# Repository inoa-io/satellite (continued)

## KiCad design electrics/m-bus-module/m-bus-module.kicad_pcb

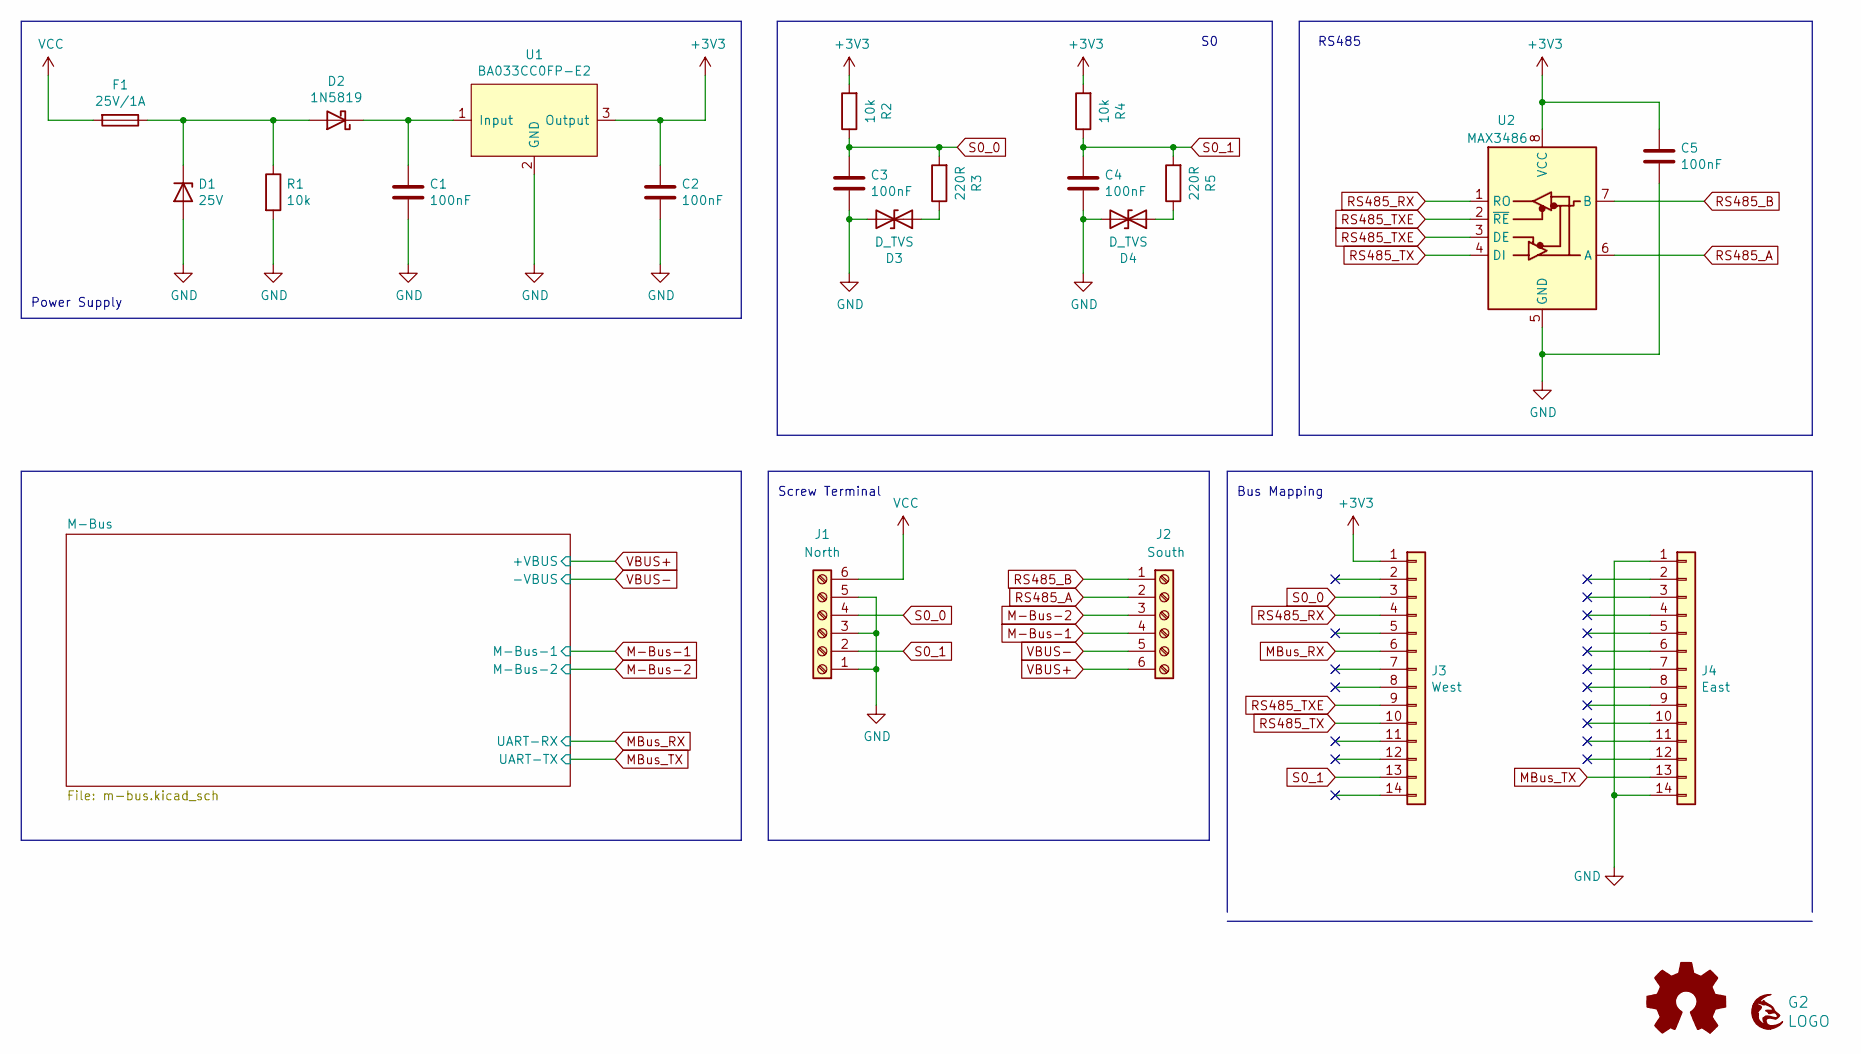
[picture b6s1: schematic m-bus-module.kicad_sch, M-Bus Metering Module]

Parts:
C1, C2, C3, C4: 100nF; C_1206_3216Metric_Pad1.33x1.80mm_HandSolder; mouser# 80-C1206C104M6R
C5: 100nF; C_0603_1608Metric_Pad1.08x0.95mm_HandSolder; mouser# 80-C1206C104M6R
D1: 25V; D_SOD-523; mouser# 750-CPDU24V
D2: 1N5819; D_SOD-323_HandSoldering; mouser# 771-PMEG4010CEAX
D3, D4: D_TVS; D_0603_1608Metric_Pad1.05x0.95mm_HandSolder; mouser# 652-CG0603MLC-3.3LE
F1: 25V/1A; Fuse_1206_3216Metric_Pad1.42x1.75mm_HandSolder; mouser# 504-TR/3216FF1-R
G1: Logo_Open_Hardware_Small; OSHW-Logo2_7.3x6mm_SilkScreen
G2: LOGO; grayc-logo-negative
J1: North; PHOENIX_1935200; mouser# 651-1935200
J2: South; PHOENIX_1935200; mouser# 651-1935200
J3: West; PinHeader_1x14_P2.54mm_Vertical; mouser# 855-M20-9991446
J4: East; PinHeader_1x14_P2.54mm_Vertical; mouser# 855-M20-9991446
R1, R2, R4: 10k; R_1206_3216Metric_Pad1.30x1.75mm_HandSolder; mouser# 652-CR1206JW-103ELF
R3, R5: 220R; R_1206_3216Metric_Pad1.30x1.75mm_HandSolder; mouser# 652-CR0603FX-2200ELF
U1: BA033CC0FP-E2; TO-252-3_TabPin2; mouser# 755-BA033CC0FP-E2
U2: MAX3486; SOIC-8_3.9x4.9mm_P1.27mm; mouser# 700-MAX3486EESA

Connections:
+3V3: C2.1, C5.1, J3.1, R2.2, R4.2, U1.3 (Output), U2.8 (VCC); also elsewhere on the board
GND: C1.2, C2.2, C3.2, C4.2, C5.2, D1.2 (A), D3.2 (A2), D4.2 (A2), J1.1, J1.3, J1.5, J4.1, J4.14, R1.2, U1.2 (GND), U2.5 (GND); also elsewhere on the board
GNDS: J2.3, J2.5; also elsewhere on the board
M-Bus: J2.4; also elsewhere on the board
MBus_RX: J3.6; also elsewhere on the board
MBus_TX: J4.13; also elsewhere on the board
unnamed: C1.1, D2.1 (K), U1.1 (Input)
unnamed: D1.1 (K), D2.2 (A), F1.1, R1.1
unnamed: D3.1 (A1), R3.1
unnamed: D4.1 (A1), R5.1
RS485_A: J2.2, U2.6 (A)
RS485_B: J2.1, U2.7 (B)
RS485_RX: J3.4, U2.1 (RO)
RS485_TX: J3.10, U2.4 (DI)
RS485_TXE: J3.9, U2.2 (~RE), U2.3 (DE)
S0_0: C3.1, J1.4, J3.3, R2.1, R3.2
S0_1: C4.1, J1.2, J3.13, R4.1, R5.2
VBUS: J2.6; also elsewhere on the board
VCC: F1.2, J1.6

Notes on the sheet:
Bus Mapping
RS485
Power Supply
Screw Terminal

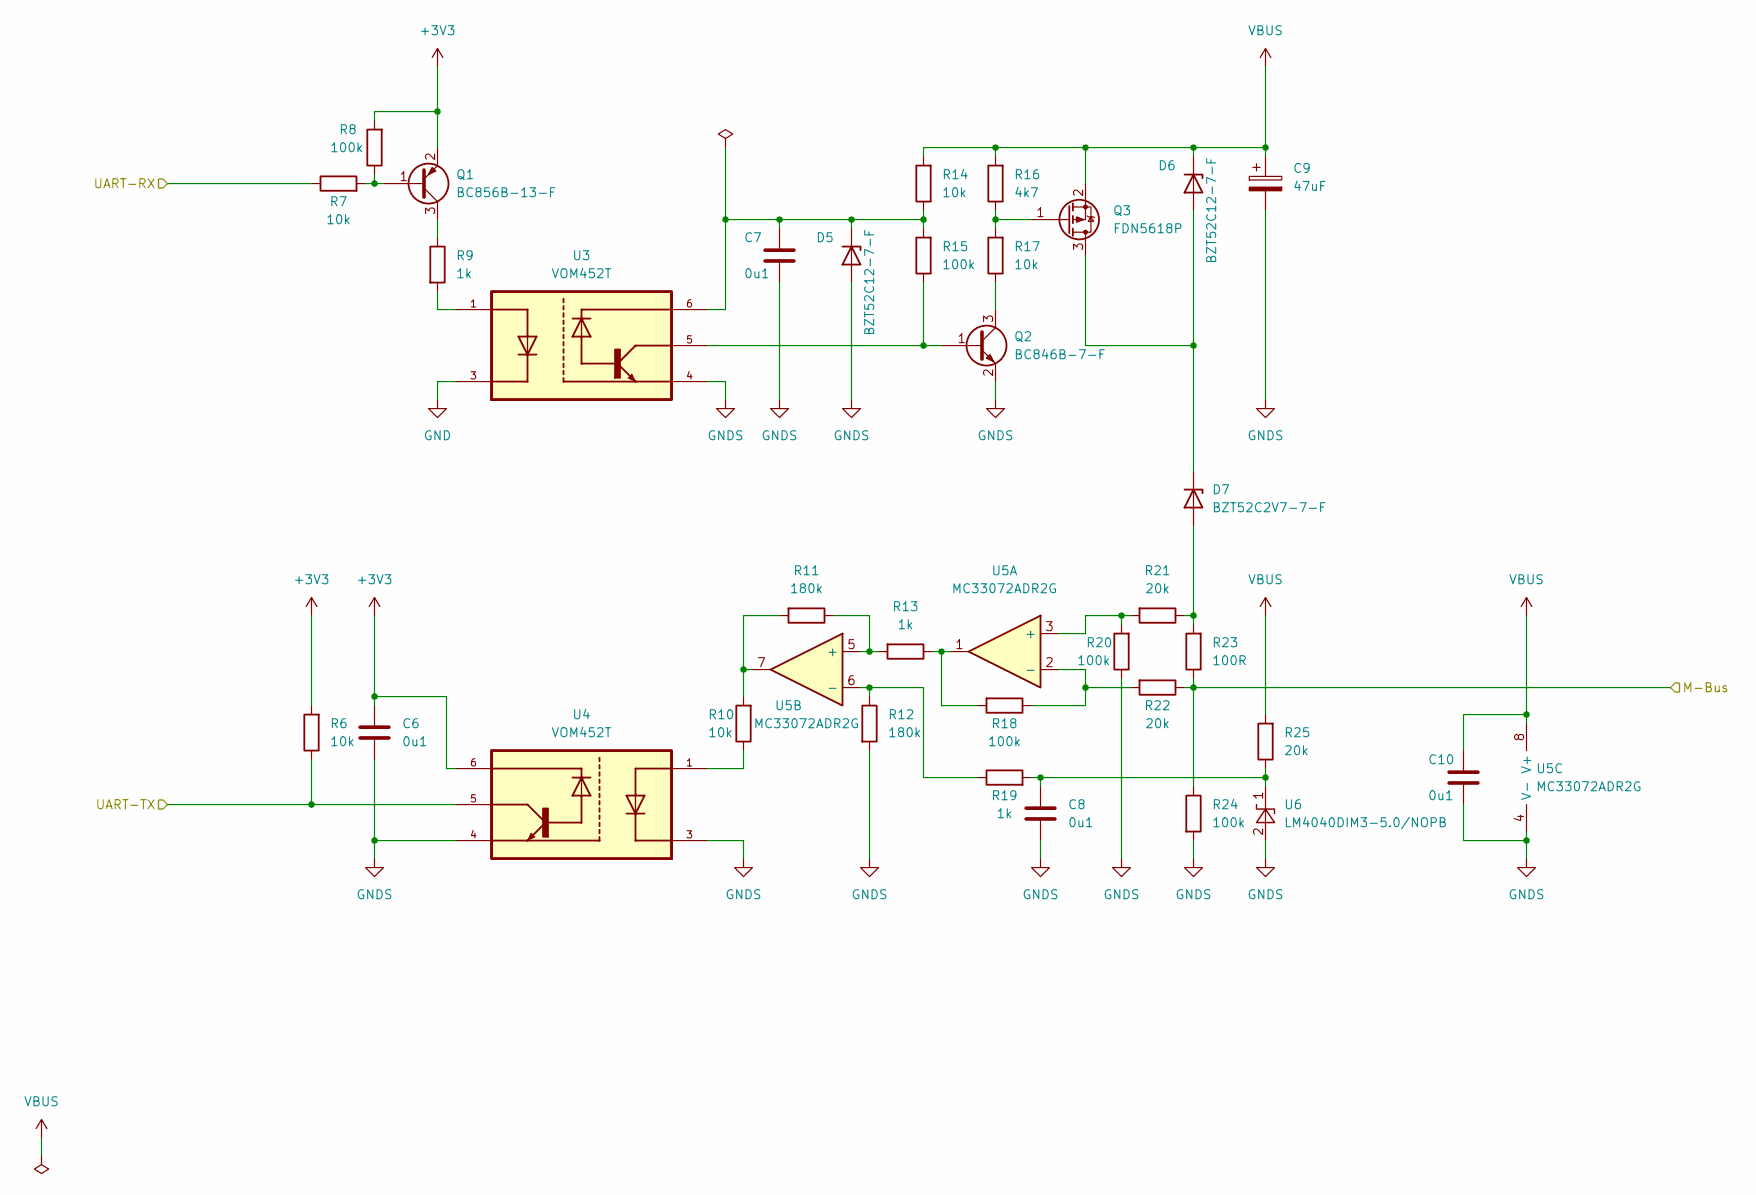
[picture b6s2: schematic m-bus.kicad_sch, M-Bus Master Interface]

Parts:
C6, C7, C8, C10: 0u1; C_0603_1608Metric_Pad1.08x0.95mm_HandSolder; mouser# 80-C0603C104M4R
C9: 47uF; CP_Elec_6.3x7.7; mouser# 80-EDK476M050S9HAA
D5, D6: BZT52C12-7-F; D_SOD-123; mouser# 621-BZT52C12-F
D7: BZT52C2V7-7-F; D_SOD-123; mouser# 621-BZT52C2V7-F
Q1: BC856B-13-F; SOT-23; mouser# 621-BC856B-13-F
Q2: BC846B-7-F; SOT-23; mouser# 621-BC846B-7-F
Q3: FDN5618P; SOT-23; mouser# 78-SI2309CDS-T1-BE3
R6, R7, R10, R14, R17: 10k; R_0603_1608Metric_Pad0.98x0.95mm_HandSolder; mouser# 660-RN73H1TD1002F25
R8, R15, R18, R20, R24: 100k; R_0603_1608Metric_Pad0.98x0.95mm_HandSolder; mouser# 660-RN73H1JTD1003F25
R9, R13, R19: 1k; R_0603_1608Metric_Pad0.98x0.95mm_HandSolder; mouser# 660-RN73H1JTD1001B25
R11, R12: 180k; R_0603_1608Metric_Pad0.98x0.95mm_HandSolder; mouser# 660-RN73H1JTD1803F25
R16: 4k7; R_0603_1608Metric_Pad0.98x0.95mm_HandSolder; mouser# 660-RN73H1JT4701F100
R21, R22, R25: 20k; R_0603_1608Metric_Pad0.98x0.95mm_HandSolder; mouser# 660-RN73H1JTD2002B10
R23: 100R; R_0603_1608Metric_Pad0.98x0.95mm_HandSolder; mouser# 660-RN73H1JTD1000F50
U3, U4: VOM452T; SOIC127P700X230-5N; mouser# 782-VOM452T
U5: MC33072ADR2G; SOIC127P600X175-8N; mouser# 511-LM258ADT
U6: LM4040DIM3-5.0/NOPB; SOT-23; mouser# 926-LM4040DIM350NOPB

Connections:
+3V3: C6.1, Q1.2 (E), R6.2, R8.2, U4.6; also elsewhere on the board
GND: U3.3; also elsewhere on the board
GNDS: C6.2, C7.2, C8.2, C9.2, C10.2, D5.2 (A), Q2.2 (E), R12.2, R20.1, R24.2, U3.4, U4.3, U4.4, U5.4 (V-), U6.2 (A); also elsewhere on the board
M-Bus: R22.1, R23.1, R24.1; also elsewhere on the board
MBus_RX: R7.1; also elsewhere on the board
MBus_TX: R6.1, U4.5; also elsewhere on the board
unnamed: C7.1, D5.1 (K), R14.1, R15.2, U3.6
unnamed: C8.1, R19.2, R25.1, U6.1 (K)
unnamed: D6.2 (A), D7.1 (K), Q3.3 (D)
unnamed: D7.2 (A), R21.1, R23.2
unnamed: Q1.1 (B), R7.2, R8.1
unnamed: Q1.3 (C), R9.1
unnamed: Q2.1 (B), R15.1, U3.5
unnamed: Q2.3 (C), R17.1
unnamed: Q3.1 (G), R16.1, R17.2
unnamed: R9.2, U3.1
unnamed: R10.1, U4.1
unnamed: R10.2, R11.2, U5.7
unnamed: R11.1, R13.2, U5.5 (+)
unnamed: R12.1, R19.1, U5.6 (-)
unnamed: R13.1, R18.2, U5.1
unnamed: R18.1, R22.2, U5.2 (-)
unnamed: R20.2, R21.2, U5.3 (+)
VBUS: C9.1, C10.1, D6.1 (K), Q3.2 (S), R14.2, R16.2, R25.2, U5.8 (V+); also elsewhere on the board

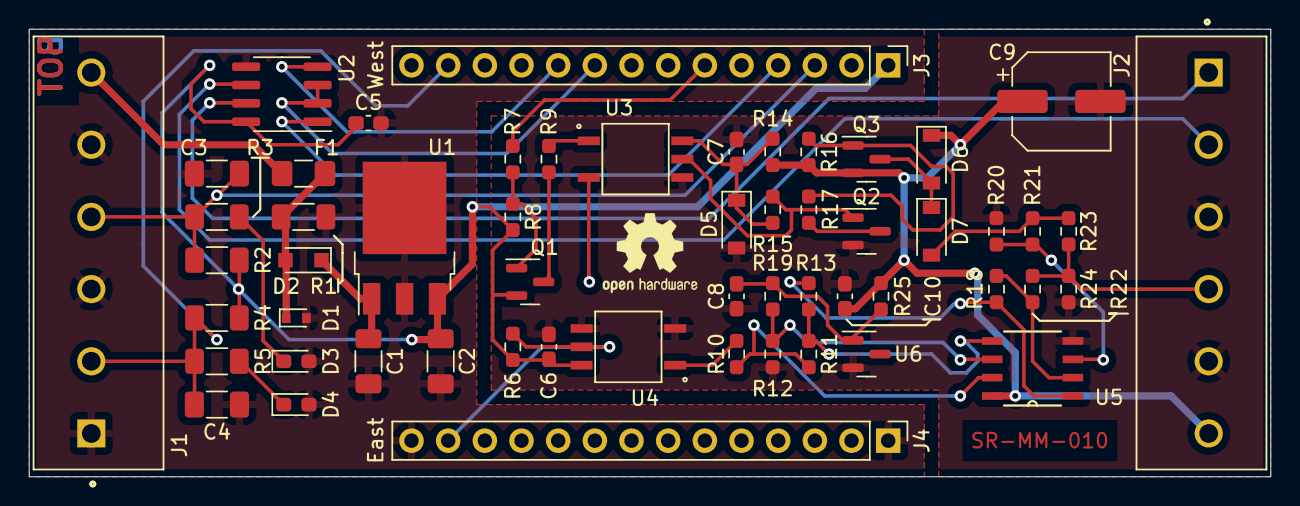
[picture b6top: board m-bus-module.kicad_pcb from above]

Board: 2 copper layers, 86.0 x 31.0 mm, 58 parts (1 on the bottom side), 36 nets.

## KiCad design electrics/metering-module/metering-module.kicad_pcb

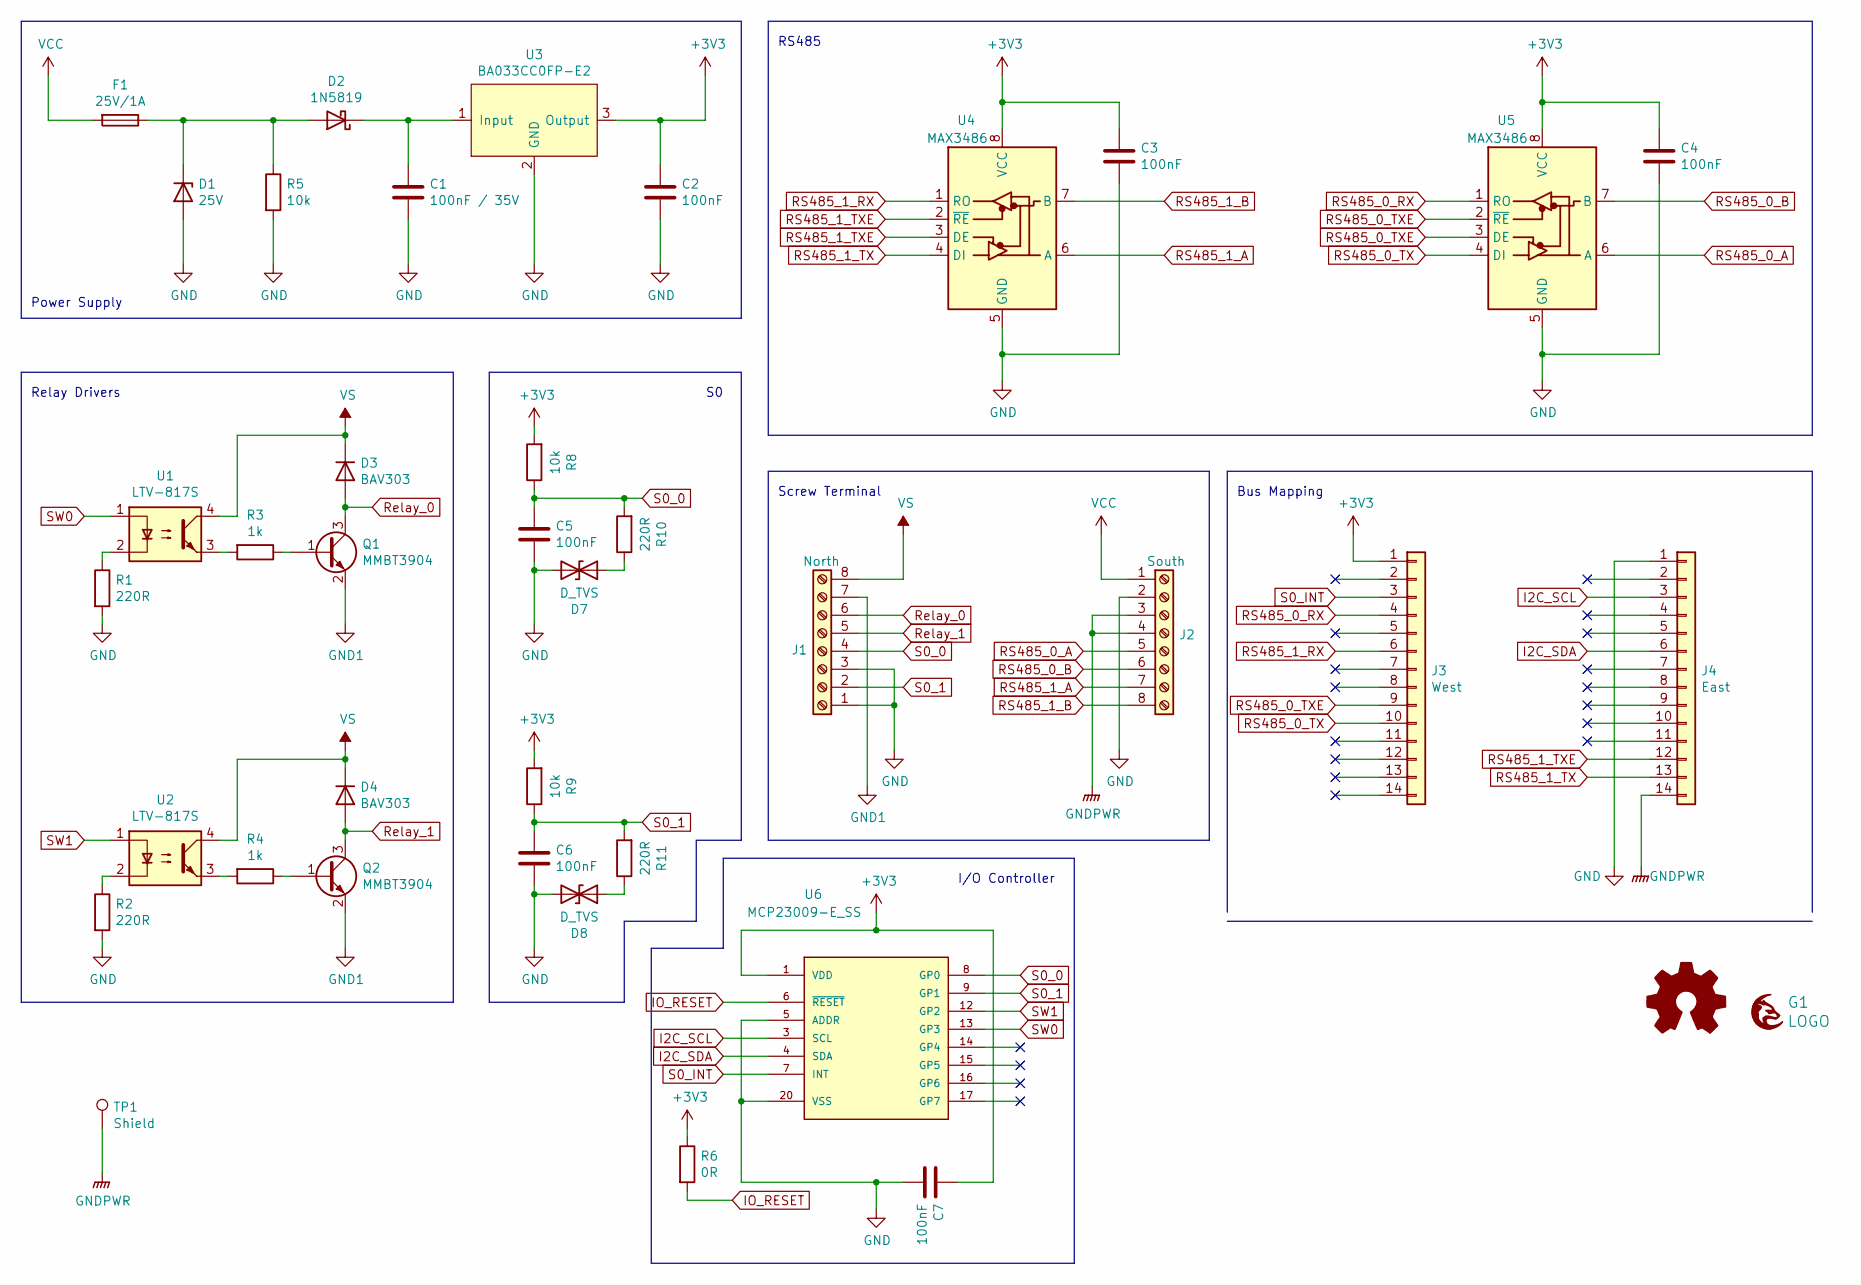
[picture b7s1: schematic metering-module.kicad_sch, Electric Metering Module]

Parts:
C1: 100nF / 35V; C_1206_3216Metric_Pad1.33x1.80mm_HandSolder
C2, C3, C4, C5, C6, C7: 100nF; C_1206_3216Metric_Pad1.33x1.80mm_HandSolder
D1: 25V; D_SOD-523
D2: 1N5819; D_SOD-323_HandSoldering
D3, D4: BAV303; D_MicroMELF
D7, D8: D_TVS; D_0603_1608Metric_Pad1.05x0.95mm_HandSolder
F1: 25V/1A; Fuse_1206_3216Metric_Pad1.42x1.75mm_HandSolder
G1: LOGO; grayc-logo-negative
G2: Logo_Open_Hardware_Small; OSHW-Logo2_7.3x6mm_SilkScreen
J1: North; PHOENIX_1727078
J2: South; PHOENIX_1727078
J3: West; PinHeader_1x14_P2.54mm_Vertical
J4: East; PinHeader_1x14_P2.54mm_Vertical
Q1, Q2: MMBT3904; SOT-23
R1, R2, R10, R11: 220R; R_1206_3216Metric_Pad1.30x1.75mm_HandSolder
R3, R4: 1k; R_1206_3216Metric_Pad1.30x1.75mm_HandSolder
R5, R8, R9: 10k; R_1206_3216Metric_Pad1.30x1.75mm_HandSolder
R6: 0R; R_1206_3216Metric_Pad1.30x1.75mm_HandSolder
TP1: Shield; TestPoint_Pad_D4.0mm
U1, U2: LTV-817S; SMDIP-4_W9.53mm
U3: BA033CC0FP-E2; TO-252-3_TabPin2
U4, U5: MAX3486; SOIC-8_3.9x4.9mm_P1.27mm
U6: MCP23009-E_SS; SOP65P780X200-20N

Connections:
GND: C1.2, C2.2, C3.2, C4.2, C5.2, C6.2, C7.2, D1.2 (A), D7.2 (A2), D8.2 (A2), J1.1, J1.3, J2.2, J4.1, R1.2, R2.2, R5.2, U3.2 (GND), U4.5 (GND), U5.5 (GND), U6.5 (ADDR), U6.20 (VSS)
GND1: J1.7, Q1.2 (E), Q2.2 (E)
GNDPWR: J2.3, J2.4, J4.14, TP1.1
I2C_SCL: J4.3, U6.3 (SCL)
I2C_SDA: J4.6, U6.4 (SDA)
unnamed: C1.1, D2.1 (K), U3.1 (Input)
unnamed: D1.1 (K), D2.2 (A), F1.1, R5.1
unnamed: D7.1 (A1), R10.1
unnamed: D8.1 (A1), R11.1
unnamed: Q1.1 (B), R3.1
unnamed: Q2.1 (B), R4.1
unnamed: R1.1, U1.2
unnamed: R2.1, U2.2
unnamed: R3.2, U1.3
unnamed: R4.2, U2.3
RS485_0_A: J2.5, U5.6 (A)
RS485_0_B: J2.6, U5.7 (B)
RS485_0_RX: J3.4, U5.1 (RO)
RS485_0_TX: J3.10, U5.4 (DI)
RS485_0_TXE: J3.9, U5.2 (~RE), U5.3 (DE)
RS485_1_A: J2.7, U4.6 (A)
RS485_1_B: J2.8, U4.7 (B)
RS485_1_RX: J3.6, U4.1 (RO)
RS485_1_TX: J4.13, U4.4 (DI)
RS485_1_TXE: J4.12, U4.2 (~RE), U4.3 (DE)
Relay_0: D3.2 (A), J1.6, Q1.3 (C)
Relay_1: D4.2 (A), J1.5, Q2.3 (C)
S0_0: C5.1, J1.4, R8.1, R10.2, U6.8 (GP0)
S0_1: C6.1, J1.2, R9.1, R11.2, U6.9 (GP1)
S0_INT: J3.3, U6.7 (INT)
SW0: U1.1, U6.13 (GP3)
SW1: U2.1, U6.12 (GP2)
VCC: F1.2, J2.1
VS: D3.1 (K), D4.1 (K), J1.8, U1.4, U2.4

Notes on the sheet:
Relay Drivers
RS485
Screw Terminal
I/O Controller
Bus Mapping
Power Supply

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
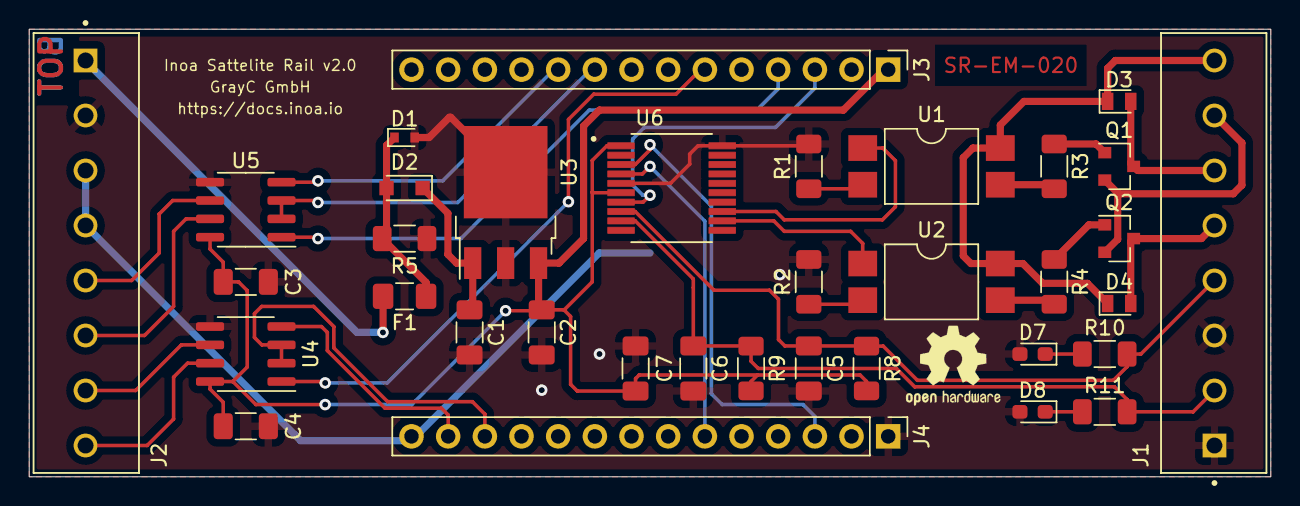
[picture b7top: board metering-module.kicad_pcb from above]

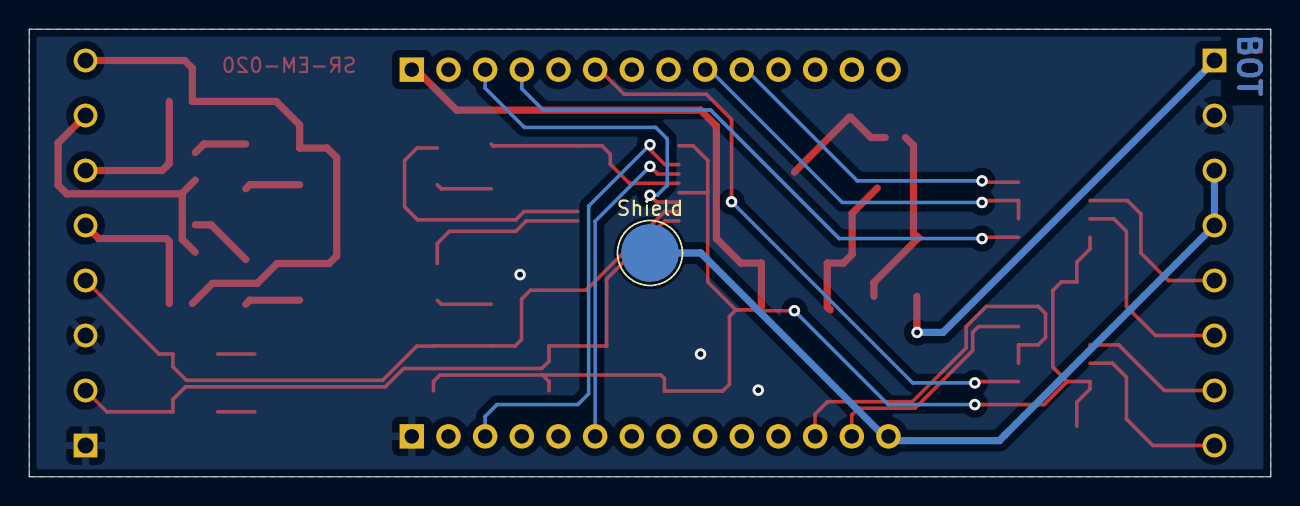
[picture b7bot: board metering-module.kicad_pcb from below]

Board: 2 copper layers, 86.0 x 31.0 mm, 38 parts (2 on the bottom side), 35 nets.

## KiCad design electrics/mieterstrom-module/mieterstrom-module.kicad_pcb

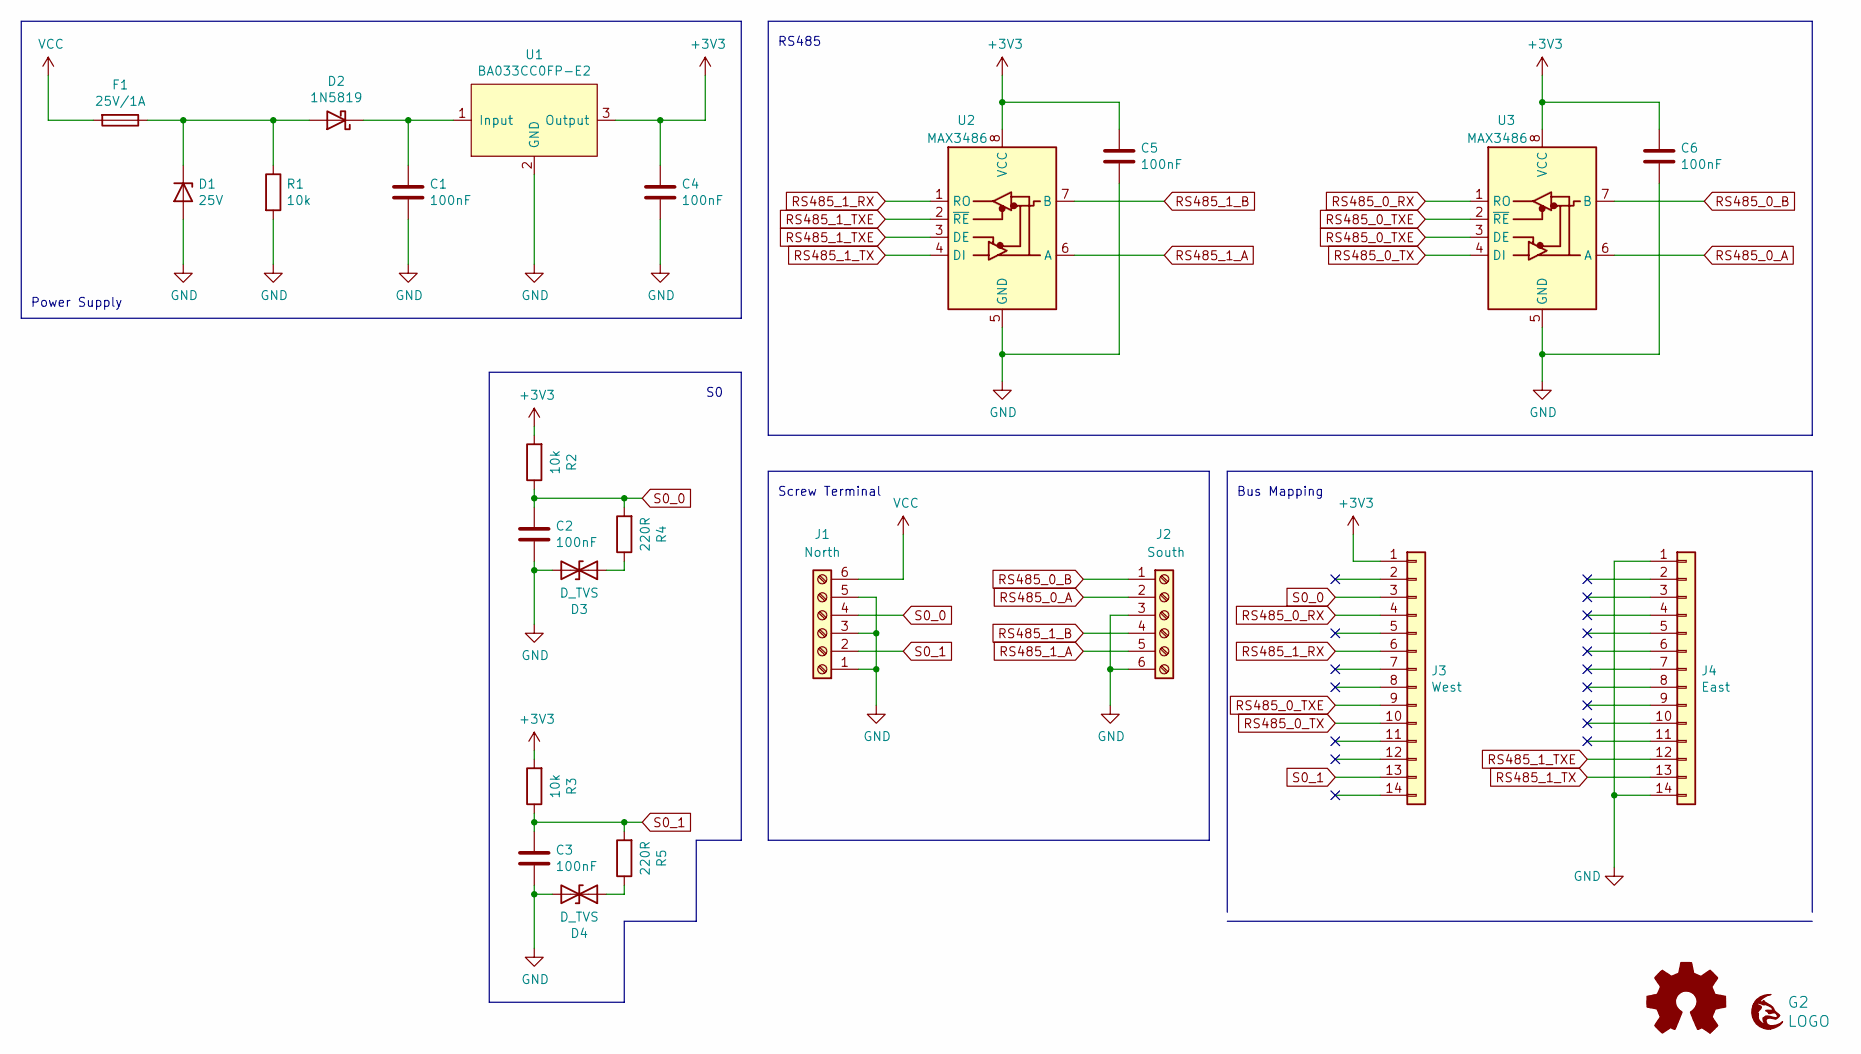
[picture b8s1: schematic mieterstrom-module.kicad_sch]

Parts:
C1, C2, C3, C4, C5, C6: 100nF; C_1206_3216Metric_Pad1.33x1.80mm_HandSolder; mouser# 80-C1206C104M6R
D1: 25V; D_SOD-523; mouser# 750-CPDU24V
D2: 1N5819; D_SOD-323_HandSoldering; mouser# 771-PMEG4010CEAX
D3, D4: D_TVS; D_0603_1608Metric_Pad1.05x0.95mm_HandSolder; mouser# 652-CG0603MLC-3.3LE
F1: 25V/1A; Fuse_1206_3216Metric_Pad1.42x1.75mm_HandSolder; mouser# 504-TR/3216FF1-R
G1: Logo_Open_Hardware_Small; OSHW-Logo2_7.3x6mm_SilkScreen
G2: LOGO; grayc-logo-negative
J1: North; PHOENIX_1935200; mouser# 651-1935200
J2: South; PHOENIX_1935200; mouser# 651-1935200
J3: West; PinHeader_1x14_P2.54mm_Vertical; mouser# 855-M20-9991446
J4: East; PinHeader_1x14_P2.54mm_Vertical; mouser# 855-M20-9991446
R1, R2, R3: 10k; R_1206_3216Metric_Pad1.30x1.75mm_HandSolder; mouser# 652-CR1206JW-103ELF
R4, R5: 220R; R_1206_3216Metric_Pad1.30x1.75mm_HandSolder; mouser# 652-CR0603FX-2200ELF
U1: BA033CC0FP-E2; TO-252-3_TabPin2; mouser# 755-BA033CC0FP-E2
U2, U3: MAX3486; SOIC-8_3.9x4.9mm_P1.27mm; mouser# 700-MAX3486EESA

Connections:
+3V3: C4.1, C5.1, C6.1, J3.1, R2.2, R3.2, U1.3 (Output), U2.8 (VCC), U3.8 (VCC)
GND: C1.2, C2.2, C3.2, C4.2, C5.2, C6.2, D1.2 (A), D3.2 (A2), D4.2 (A2), J1.1, J1.3, J1.5, J2.3, J2.6, J4.1, J4.14, R1.2, U1.2 (GND), U2.5 (GND), U3.5 (GND)
unnamed: C1.1, D2.1 (K), U1.1 (Input)
unnamed: D1.1 (K), D2.2 (A), F1.1, R1.1
unnamed: D3.1 (A1), R4.1
unnamed: D4.1 (A1), R5.1
RS485_0_A: J2.2, U3.6 (A)
RS485_0_B: J2.1, U3.7 (B)
RS485_0_RX: J3.4, U3.1 (RO)
RS485_0_TX: J3.10, U3.4 (DI)
RS485_0_TXE: J3.9, U3.2 (~RE), U3.3 (DE)
RS485_1_A: J2.5, U2.6 (A)
RS485_1_B: J2.4, U2.7 (B)
RS485_1_RX: J3.6, U2.1 (RO)
RS485_1_TX: J4.13, U2.4 (DI)
RS485_1_TXE: J4.12, U2.2 (~RE), U2.3 (DE)
S0_0: C2.1, J1.4, J3.3, R2.1, R4.2
S0_1: C3.1, J1.2, J3.13, R3.1, R5.2
VCC: F1.2, J1.6

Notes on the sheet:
Bus Mapping
RS485
Power Supply
Screw Terminal

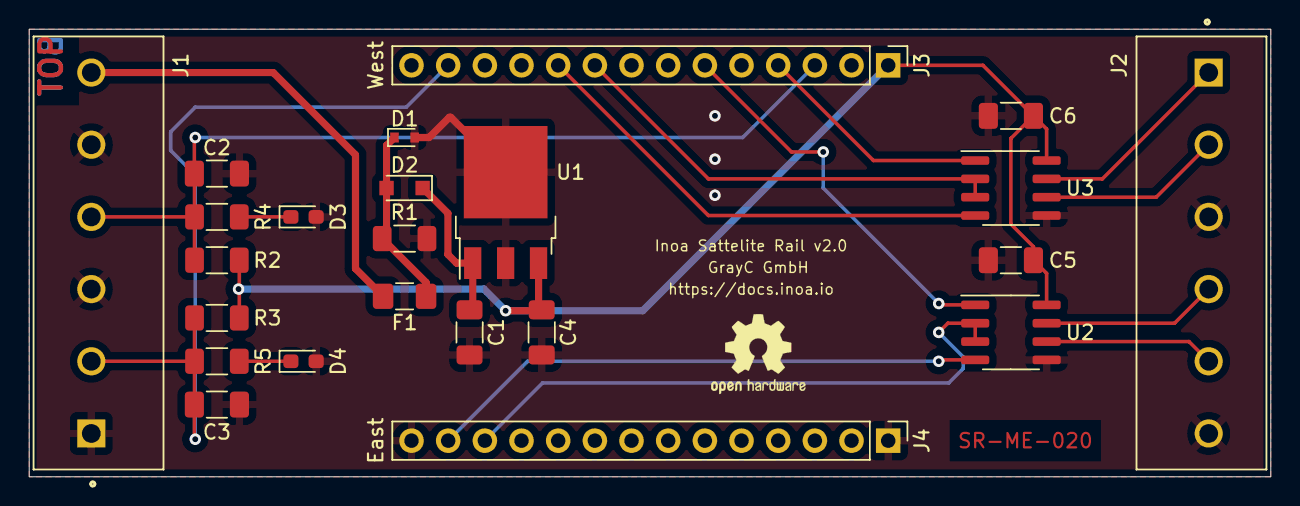
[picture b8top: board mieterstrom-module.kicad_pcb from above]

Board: 2 copper layers, 86.0 x 31.0 mm, 25 parts (1 on the bottom side), 19 nets.
